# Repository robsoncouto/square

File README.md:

# Square wave mini keyboard

This is something I cretaed whitin a day, board and code. Have been trying to prone my pcb making skills.

This is inpired by the [8-Bit Capacitive Synth](https://support.bantamtools.com/hc/en-us/articles/360001045893?_ga=2.258280015.458448953.1538141580-1372417667.1536370002) from Bantam tools.

## Features

Sound part, nothing special, just a single plain sqaure wave.

The board uses capcitive pads, my fisrt time experimenting with em, I'm quite impresssed with the simplicity and reliability.

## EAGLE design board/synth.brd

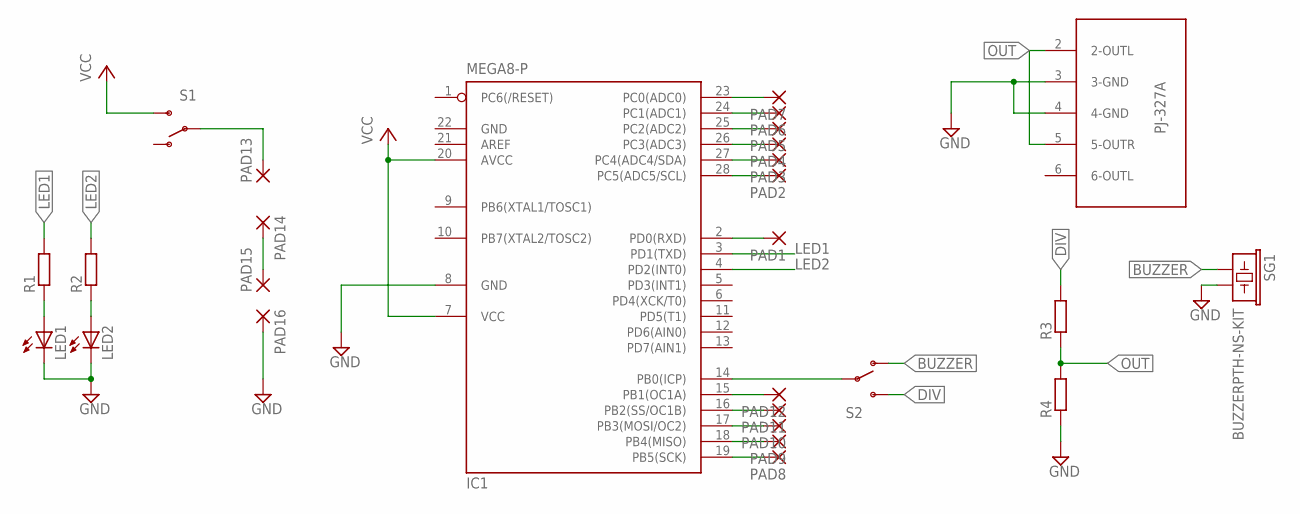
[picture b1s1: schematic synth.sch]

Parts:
IC1: MEGA8-P; DIL28-3
LED1, LED2: LEDSML0805; SML0805
PAD1, PAD2, PAD3, PAD4, PAD5, PAD6, PAD7, PAD8, PAD9, PAD10, PAD11, PAD12: SMD2; SMD1,27-2,54
PAD13, PAD14, PAD15, PAD16: 2,54/1,1
R1, R2, R3, R4: R-EU_R0805; R0805
S1, S2: SWITCH-SPDTPTH; SWITCH-SPDT
SG1: BUZZERPTH-NS-KIT; BUZZER-12MM-NS-KIT
U$1: PJ-327A

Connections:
BUZZER: S2.1 (O), SG1.+ (1)
DIV: R3.2, S2.3 (S)
GND: IC1.8 (GND), IC1.22 (GND), LED1.C, LED2.C, PAD16.1, R4.1, SG1.- (2), U$1.3 (3-GND), U$1.4 (4-GND)
LED1: IC1.3 (PD1(TXD)), R1.2
LED2: IC1.4 (PD2(INT0)), R2.2
unnamed: LED1.A, R1.1
unnamed: PAD14.1, PAD15.1
unnamed: LED2.A, R2.1
unnamed: PAD13.1, S1.2
unnamed: IC1.14 (PB0(ICP)), S2.2
OUT: R3.1, R4.2, U$1.2 (2-OUTL), U$1.5 (5-OUTR)
PAD1: IC1.2 (PD0(RXD)), PAD1.1
PAD2: IC1.28 (PC5(ADC5/SCL)), PAD2.1
PAD3: IC1.27 (PC4(ADC4/SDA)), PAD3.1
PAD4: IC1.26 (PC3(ADC3)), PAD4.1
PAD5: IC1.25 (PC2(ADC2)), PAD5.1
PAD6: IC1.24 (PC1(ADC1)), PAD6.1
PAD7: IC1.23 (PC0(ADC0)), PAD7.1
PAD8: IC1.19 (PB5(SCK)), PAD8.1
PAD9: IC1.18 (PB4(MISO)), PAD9.1
PAD10: IC1.17 (PB3(MOSI/OC2)), PAD10.1
PAD11: IC1.16 (PB2(SS/OC1B)), PAD11.1
PAD12: IC1.15 (PB1(OC1A)), PAD12.1
VCC: IC1.7 (VCC), IC1.20 (AVCC), S1.3 (S)

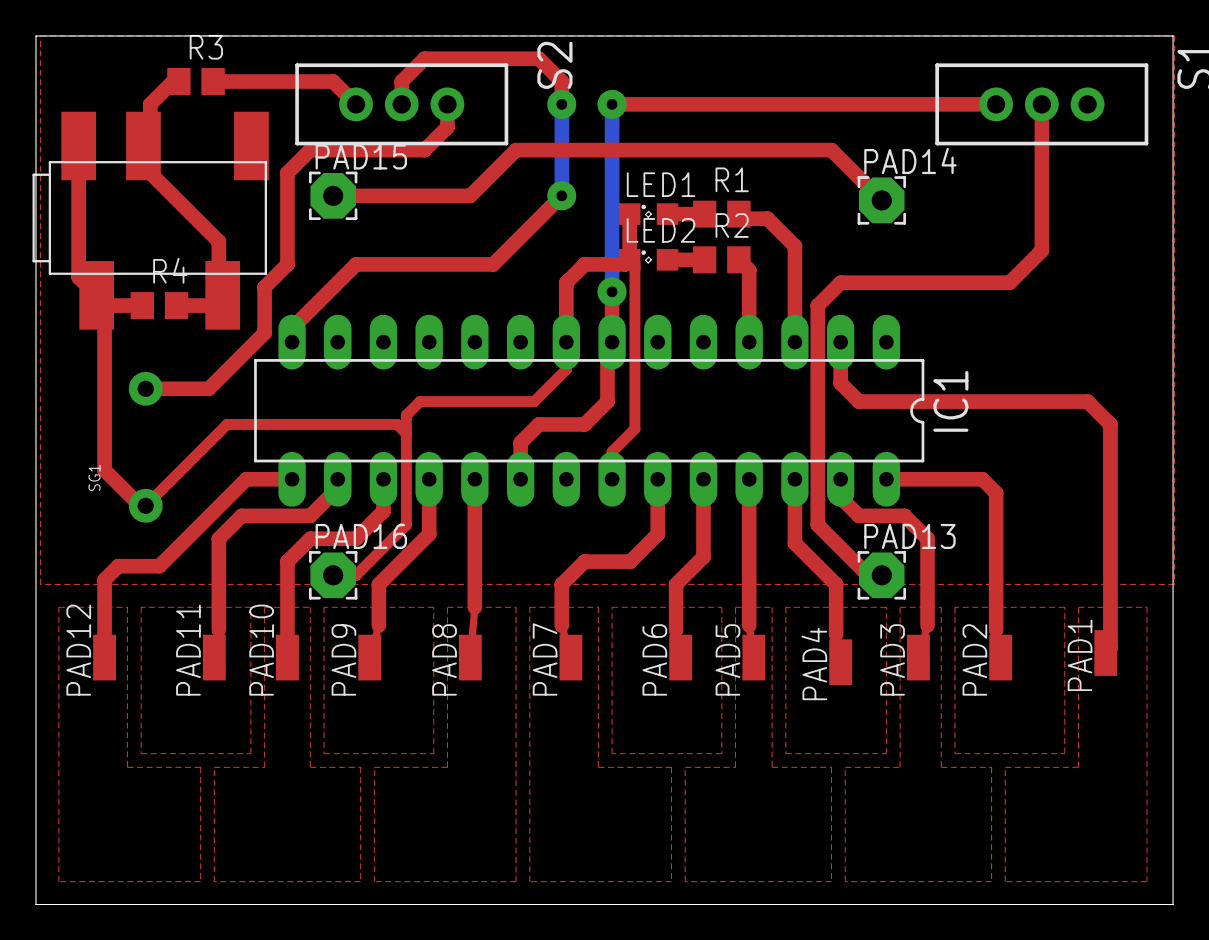
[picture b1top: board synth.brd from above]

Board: 2 copper layers, 63.2 x 48.2 mm, 27 parts (0 on the bottom side), 24 nets.

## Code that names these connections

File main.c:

#define F_CPU 8000000UL

#include<avr/io.h>
#include<util/delay.h>
#include"sound.h"

int main(void){

  DDRD=(1<<PD0)|(1<<PD2)|(1<<PD1);  
  PORTD=0x02;
  //PORTB|=(0b00000001);
  init_tone();
  while(1){
    PORTD^=(1<<PD2);
    PORTD^=(1<<PD1);
    if(readCapacitivePin(&PORTB, 1<<PB1)>5)play(NOTE_C4,100);
    if(readCapacitivePin(&PORTB, 1<<PB2)>5)play(NOTE_CS4,100);
    if(readCapacitivePin(&PORTB, 1<<PB3)>5)play(NOTE_D4,100);
    if(readCapacitivePin(&PORTB, 1<<PB4)>5)play(NOTE_DS4,100);
    if(readCapacitivePin(&PORTB, 1<<PB5)>5)play(NOTE_E4,100);
    
    if(readCapacitivePin(&PORTC, 1<<PC0)>5)play(NOTE_F4,100);
    if(readCapacitivePin(&PORTC, 1<<PC1)>5)play(NOTE_FS4,100);
    if(readCapacitivePin(&PORTC, 1<<PC2)>5)play(NOTE_G4,100);
    if(readCapacitivePin(&PORTC, 1<<PC3)>5)play(NOTE_GS4,100);
    if(readCapacitivePin(&PORTC, 1<<PC4)>5)play(NOTE_A4,100);
    if(readCapacitivePin(&PORTC, 1<<PC5)>5)play(NOTE_AS4,100);
    
    if(readCapacitivePin(&PORTD, 1<<PD0)>5)play(NOTE_B4,100);

  }
}

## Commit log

2018-09-28 Added code files to project
2018-09-28 Added file with the note frequencies
2018-09-28 Added README
2018-09-28 Added eagle files to project
2018-10-03 Added picture of the board layout

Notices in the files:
parts and their libraries:
SparkFun-Electromechanical: Licensing: Creative Commons ShareAlike 4.0 International - https://creativecommons.org/licenses/by-sa/4.0
